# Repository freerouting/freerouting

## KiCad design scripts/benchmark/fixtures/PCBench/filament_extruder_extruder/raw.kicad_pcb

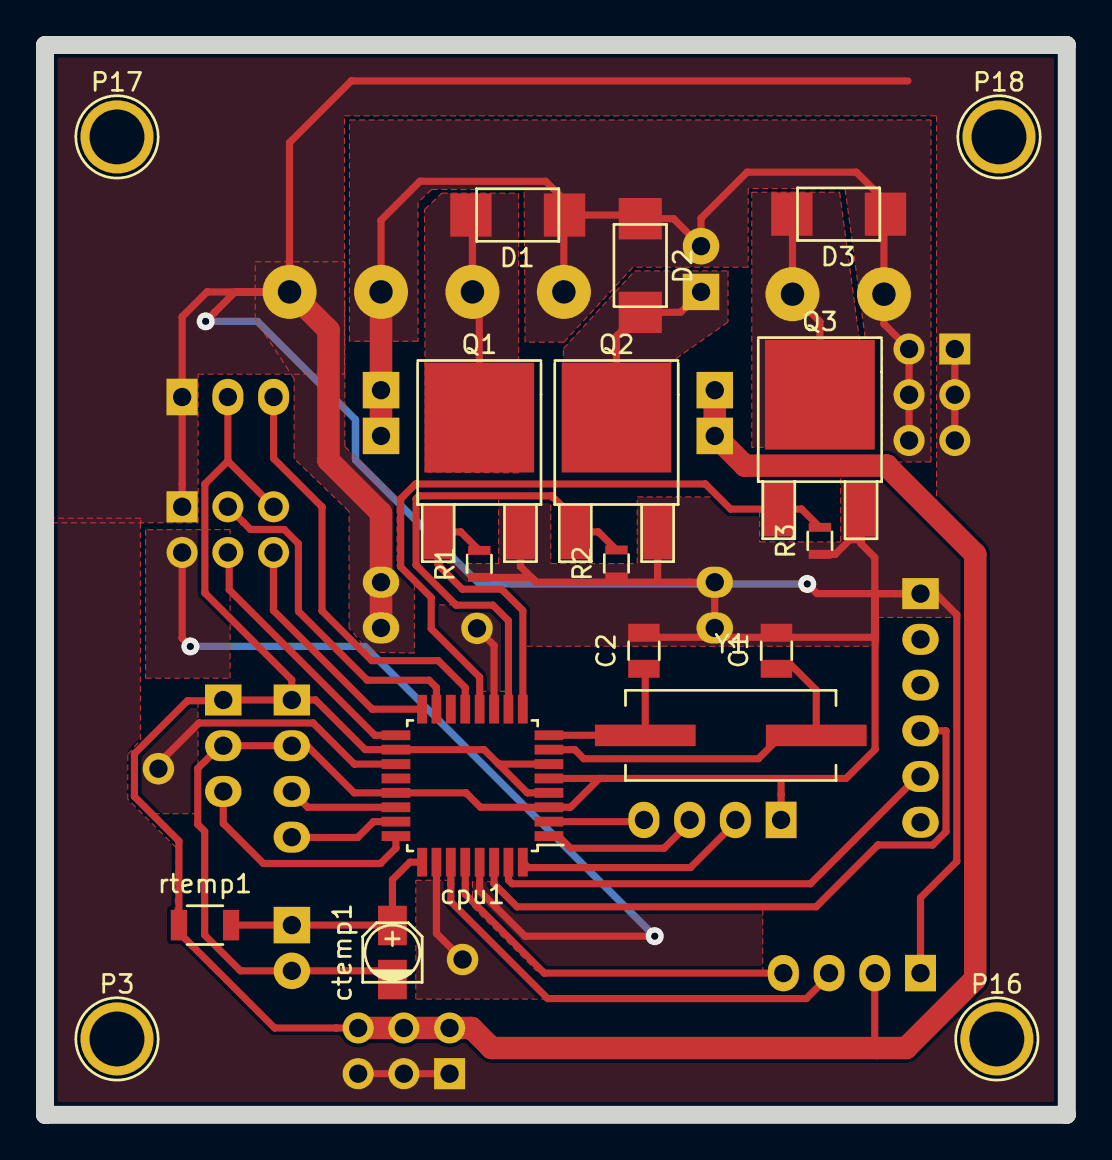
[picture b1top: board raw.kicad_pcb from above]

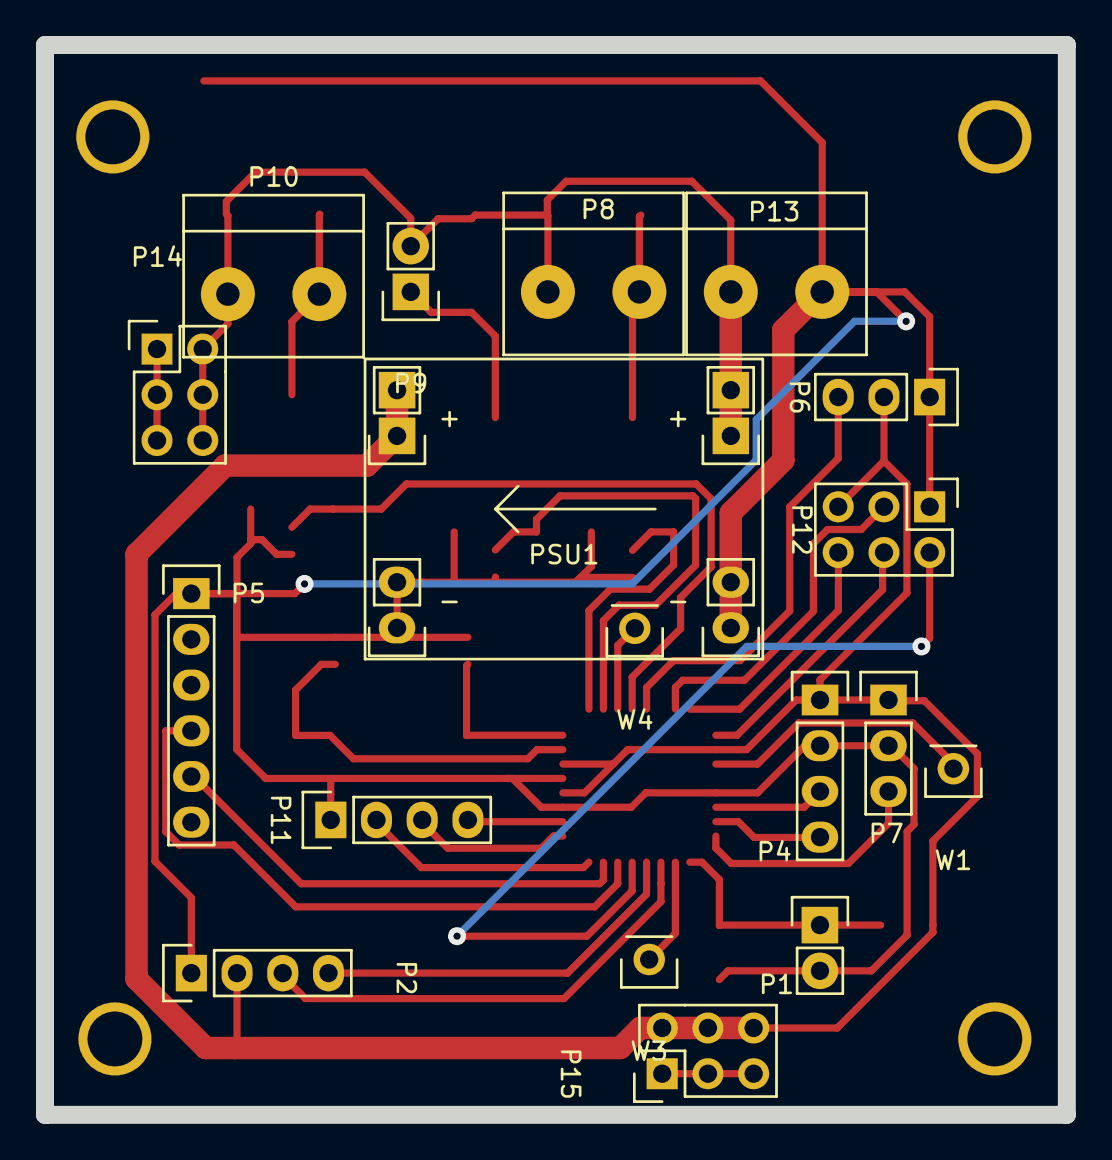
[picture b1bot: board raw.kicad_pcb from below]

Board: 2 copper layers, 56.8 x 59.4 mm, 37 parts (18 on the bottom side), 30 nets.

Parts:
C1, C2: C22pF; C_0805
D1, D2, D3: D; DO-214AC
P1: therm; Pin_Header_Straight_1x02
P2: lcd; Pin_Header_Straight_1x04
P3, P16, P17, P18: CONN_01X01; 1pin
P4: qc; Pin_Header_Straight_1x04
P5: ftdi; Pin_Header_Straight_1x06
P6: servo; Pin_Header_Straight_1x03
P7: hall; Pin_Header_Straight_1x03
P8: htr; 2Screw
P9: winder; Pin_Header_Straight_1x02
P10: auger; 2Screw
P11: enc; Pin_Header_Straight_1x04
P12: icsp; Pin_Header_Straight_2x03
P13: pwr; 2Screw
P14: 24V; Pin_Header_Straight_2x03
P15: 5V; Pin_Header_Straight_2x03
PSU1: DC-DC_Buck; 7-28V
Q1, Q2, Q3: IRLR2905PBF; TO-252-2Lead
R1, R2, R3: R100k; R_0603
W1, W3, W4: TEST_1P; Pin_Header_Straight_1x01
Y1: Crystal; Crystal_HC49-SD_SMD
cpu1: ATMEGA328P-A; TQFP-32_7x7mm_Pitch0.8mm
ctemp1: CP10uF; c_elec_3x5.3
rtemp1: R4.7k; R_1206

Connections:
+24V: D1.1, D2.1, D3.1, P8.2, P9.2, P10.2, P13.2, P14.2, P14.4, P14.6, PSU1.4
GND: C1.2, C2.2, P1.2, P2.1, P4.2, P5.1, P6.1, P7.2, P11.1, P12.1, P13.1, P14.1, P14.3, P14.5, P15.1, P15.3, P15.5, PSU1.1, PSU1.2, Q1.3, Q2.3, Q3.3, R1.1, R2.1, R3.1, cpu1.3, cpu1.5, cpu1.21, ctemp1.2
unnamed: C1.1, Y1.2, cpu1.7
unnamed: C2.1, Y1.1, cpu1.8
unnamed: D1.2, P8.1, Q1.2
unnamed: D2.2, P9.1, Q2.2
unnamed: D3.2, P10.1, Q3.2
unnamed: W1.1, cpu1.19
unnamed: W3.1, cpu1.26
unnamed: W4.1, cpu1.11
VCC: P2.2, P4.1, P6.2, P7.1, P12.5, P15.2, P15.4, P15.6, PSU1.3, cpu1.4, cpu1.6, cpu1.18, rtemp1.1
a: P11.2, cpu1.32
act: P11.4, cpu1.2
auger: Q3.1, R3.2, cpu1.12
b: P11.3, cpu1.1
diam: P4.3, cpu1.22
htr: Q1.1, R1.2, cpu1.9
length: P4.4, cpu1.23
miso: P12.6, cpu1.16
mosi: P12.3, cpu1.15
reset: P12.2, cpu1.29
rxd: P5.4, cpu1.30
sck: P12.4, cpu1.17
scl: P2.4, cpu1.28
sda: P2.3, cpu1.27
servo: P6.3, cpu1.13
spool: P7.3, cpu1.24
therm: P1.1, cpu1.25, ctemp1.1, rtemp1.2
txd: P5.5, cpu1.31
winder: Q2.1, R2.2, cpu1.10

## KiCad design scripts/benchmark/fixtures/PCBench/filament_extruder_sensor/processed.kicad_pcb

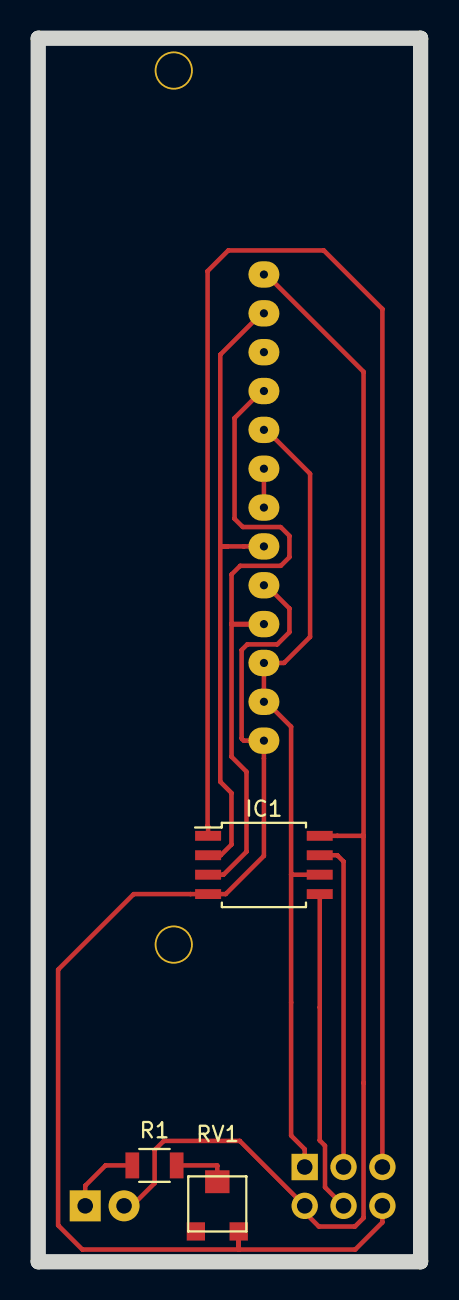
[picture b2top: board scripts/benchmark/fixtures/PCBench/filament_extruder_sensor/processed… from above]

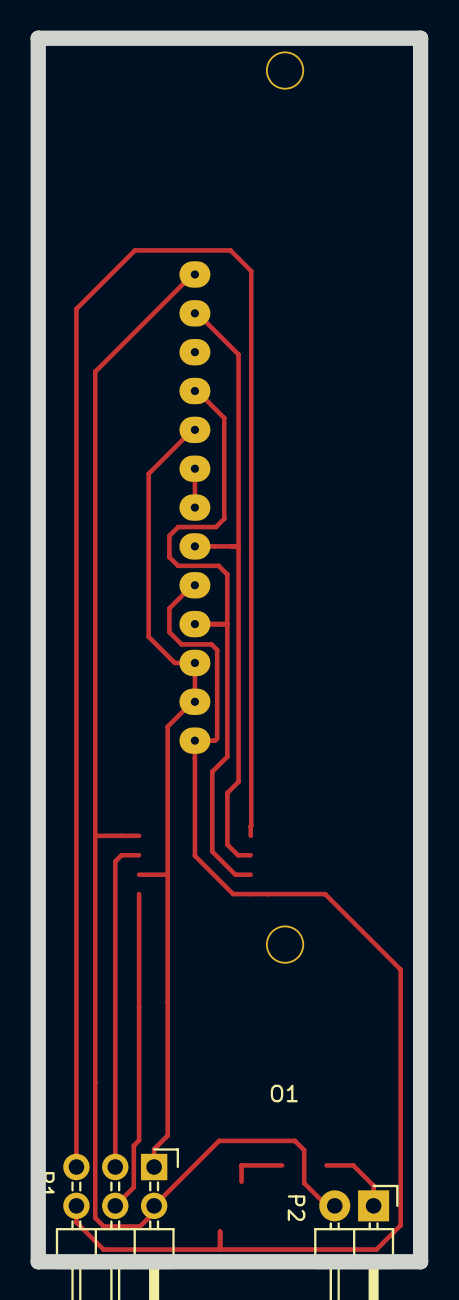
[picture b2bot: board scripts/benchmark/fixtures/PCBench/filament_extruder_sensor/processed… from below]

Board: 2 copper layers, 25.0 x 80.0 mm, 6 parts (3 on the bottom side), 11 nets.

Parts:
IC1: ATTINY45-S; SOIJ-8_5.3x5.3mm_Pitch1.27mm
O1: TSL1406R
P1: ICSP; Pin_Header_Angled_2x03
P2: LED; Pin_Header_Angled_1x02
R1: R100; R_1206
RV1: POT; Potentiometer_Trimmer-Bourne_TC33-X2

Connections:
AO: IC1.2, O1.6, O1.12
CLK: IC1.3, O1.4, O1.10
GND: IC1.4, O1.1, O1.5, P1.6, RV1.3
MISO: IC1.6, O1.2, O1.3, O1.9, P1.1
MOSI: IC1.5, P1.4
unnamed: O1.7, O1.8
unnamed: P2.1, R1.1
unnamed: R1.2, RV1.2
RESET: IC1.1, P1.5
SCK: IC1.7, P1.3
VCC: IC1.8, O1.13, P1.2, P2.2

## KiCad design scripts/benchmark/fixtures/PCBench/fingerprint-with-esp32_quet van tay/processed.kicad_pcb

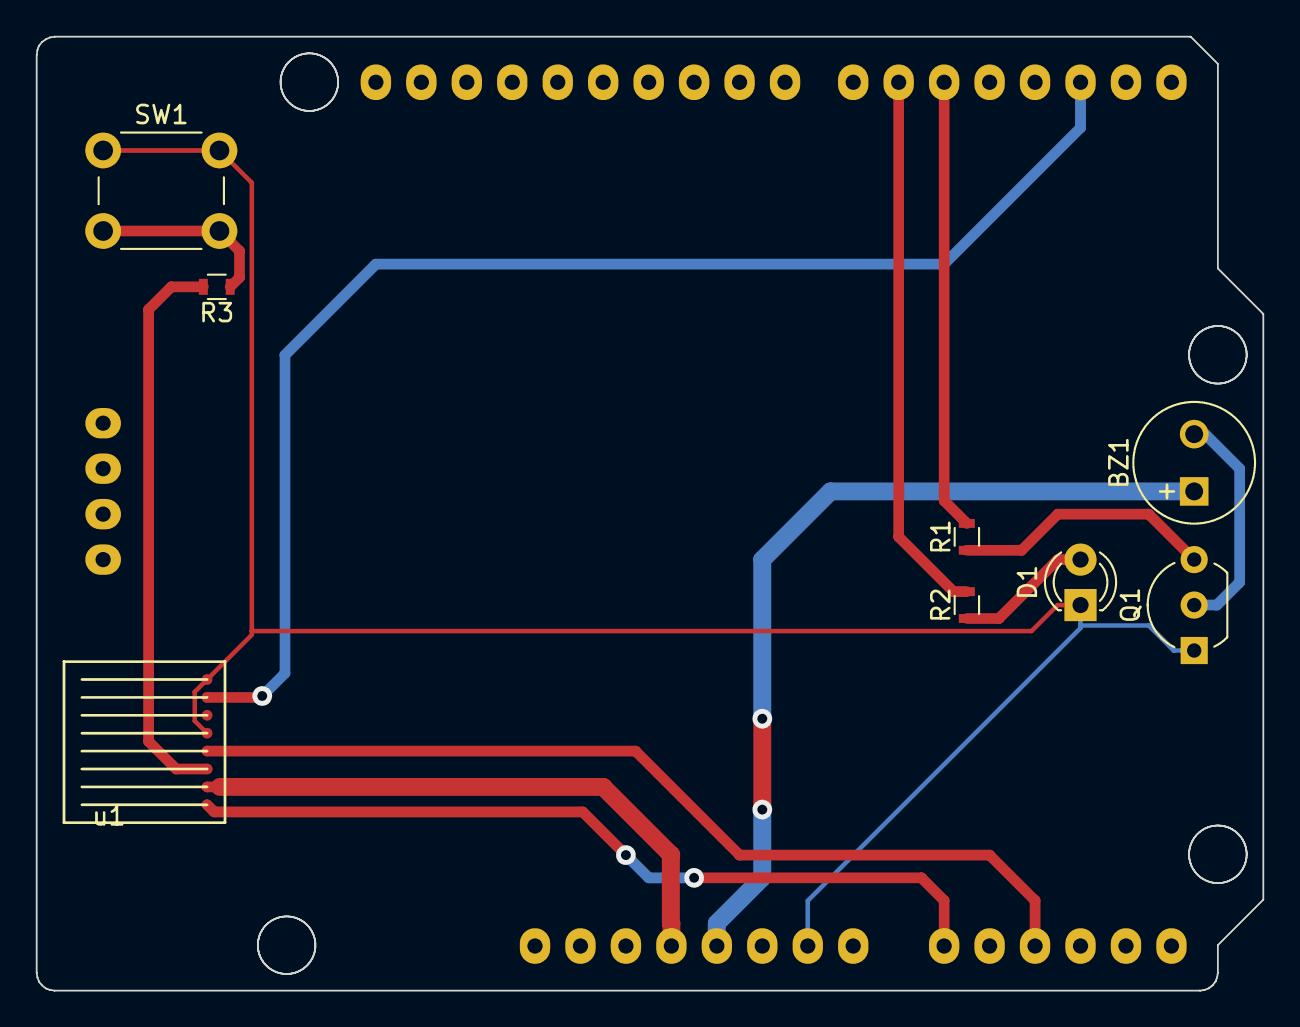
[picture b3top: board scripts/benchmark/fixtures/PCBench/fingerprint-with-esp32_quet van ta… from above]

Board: 2 copper layers, 68.5 x 53.3 mm, 9 parts (0 on the bottom side), 13 nets.

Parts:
BZ1: Buzzer; MagneticBuzzer_Kingstate_KCG0601
D1: LED; LED_D3.0mm
Q1: 2SC1815; TO-92_Inline_Wide
R1, R2: 330; R_0603
R3: 470; R_0603
S1: ESP-UNO; ESP-UNO-SH
SW1: SW_Push; SW_PUSH_6mm_h5mm
u1: fpc1011f; Pin_Header_Angled_1x08_Pitch1.27mm

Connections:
3.3V: S1.4, u1.2
5V: BZ1.1, S1.5
CLK: S1.11, u1.4
CMD: S1.17, u1.7
GND: D1.1, Q1.1, S1.7, SW1.1, u1.5, u1.8
unnamed: BZ1.2, Q1.2
unnamed: D1.2, R2.1
unnamed: Q1.3, R1.1
unnamed: R3.1, SW1.2
RST: R3.2, u1.3
SDO: S1.9, u1.1
led: R2.2, S1.21
loa: R1.2, S1.20
